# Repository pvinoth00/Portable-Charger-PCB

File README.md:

# Portable-Charger-PCB
My first PCB design used KIcad to design and prototype a Portable Charger

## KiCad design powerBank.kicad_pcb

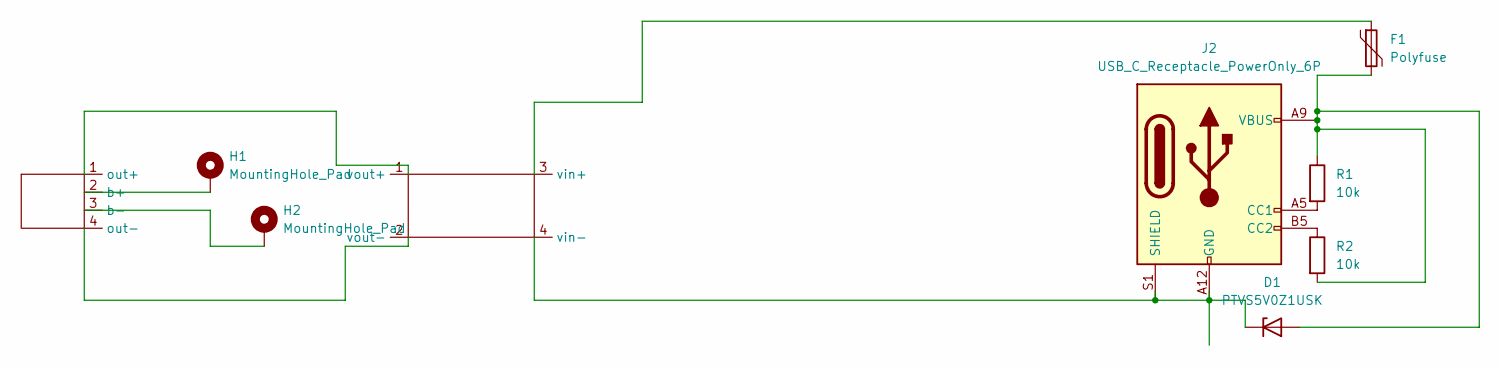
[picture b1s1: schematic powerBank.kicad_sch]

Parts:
D1: PTVS5V0Z1USK; Nexperia_DSN1608-2_1.6x0.8mm
F1: Polyfuse; Fuse_Bourns_MF-RG300
H1, H2: MountingHole_Pad; MountingHole_2.2mm_M2_DIN965_Pad
J2: USB_C_Receptacle_PowerOnly_6P; USB_C_Receptacle_GCT_USB4135-GF-A_6P_TopMnt_Horizontal
R1, R2: 10k; R_Axial_DIN0204_L3.6mm_D1.6mm_P1.90mm_Vertical
U1: 4096_module_first
U2: hw-045

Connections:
unnamed: D1.2 (A), F1.2, J2.A9 (VBUS), J2.B9 (VBUS), R1.1, R2.2
unnamed: D1.1 (K), J2.A12 (GND), J2.B12 (GND), J2.S1 (SHIELD), U2.4 (vin-)
unnamed: J2.A5 (CC1), R1.2
unnamed: J2.B5 (CC2), R2.1
unnamed: H1.1, U1.2 (b+)
unnamed: H2.1, U1.3 (b-)
unnamed: U1.1 (out+), U2.1 (vout+)
unnamed: U1.4 (out-), U2.2 (vout-)
unnamed: F1.1, U2.3 (vin+)

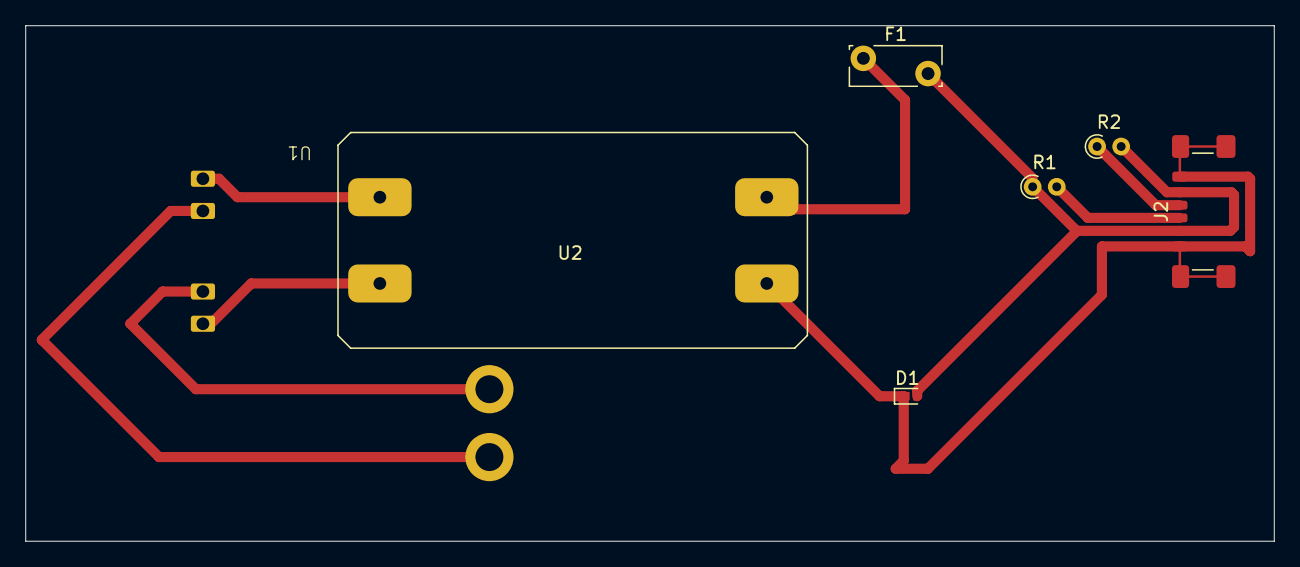
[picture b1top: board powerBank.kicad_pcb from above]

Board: 2 copper layers, 98.4 x 40.6 mm, 9 parts (0 on the bottom side), 9 nets.

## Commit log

2025-10-21 Not confirmed working
2025-10-21 adding footprints
2025-10-28 Gerber files
